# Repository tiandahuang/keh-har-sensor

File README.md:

# A Kinetic Energy Harvesting (KEH) sensor for Human Activity Recognition (HAR)
 
Design files for my thesis titled "Design of a Batteryless Sensor for Human Activity Recognition", submitted May 2024 towards an MS in Electrical and Computer Engineering at the University of Texas Austin and advised by Dr. Radu Marculescu.

## Abstract

Recent advancements in sensing technology coupled with the proliferation of
cheap, low power computing have enabled the growing popularity of wearable sensors
in everyday activities. Inertial sensing, particularly for human activity recognition
(HAR), has emerged as a ubiquitous tool across fitness, healthcare, and entertainment
applications. However, conventional wearable sensors rely on batteries, introducing
limitations in cost, environmental impact, and user burden.

This thesis explores a solution to the limitations of battery-powered operation
with the design and implementation of a wearable, kinetic energy harvesting (KEH)
powered wireless inertial sensor for batteryless HAR. The KEH-powered sensor is
energy optimized to require only 140µJ per set of accelerometer samples, translating
to an average power draw of 90µJ during continuous operation. The idle power
consumption is only 9.2µW while connected over Bluetooth. Energy harvesting is
achieved by a rotational unbalanced mass electromagnetic harvester with a peak
power output of 1.3mW.

## Device Summary

#### The full device assembly: The device is designed and assembled entirely from scratch. 

#### Component view of the entire device. Enclosures are located on the top row. There are four functional components, split between the Kinetic Energy Harvesting (KEH) Module (offset mass, rotor, stator), and the Power Conversion and Sensing/Communication Modules (PCB).

#### Full device block diagram. Energy harvested by the KEH Module (left) is converted to usable power by the Power Module (middle), which is used to sample an accelerometer and to transmit data by the Sensing Module (right). Energy storage capacitors buffer the usable power.

## Physical Design

*Files are located in `./3d/*`*

The physical operation the device centers around the KEH Module, custom-designed to address the relatively high power requirements and tight space constraints of the wearable KEH sensor. The KEH Module is a rotational unbalanced mass EM harvester; this type of harvester is implemented using a statically-mounted stator and a rotor containing a permanent magnet and an attached offset mass. 

The KEH Module and its enclosure are primarily comprised of 3D-printed polylactic acid (PLA) thermoplastic. The top of the KEH Module is a 3mm acrylic panel, stiffening the assembly and providing stability to the top of the rotor. The stator and rotor are retrieved from a 28BYJ-48 geared unipolar stepper motor. For this application, the gears are removed and the stator is modified to be bipolar. The offset mass is also constructed from PLA, with steel M3 screws and fasteners for added weight. The mass totals 8.7g with a radius of 20mm.

## Firmware Design

*Files are located in `./firmware/*`*

The firmware architecture of device adheres to an event-driven paradigm, with a target of minimizing processor occupancy. By transferring execution context between various hardware-driven interrupt handlers, the total amount of processing time can be reduced. 

Initialization must be separated into a low-level initialization and BLE initialization
due to the significant power requirements of BLE: BLE initialization includes connecting to a listening device, which has an energy budget orders of magnitude higher than low-level initialization. 

After initialization is completed (including completing a BLE connection),
context is fully transferred to a series of hardware-driven interrupts. In steady-state
operation, all system execution is triggered by a periodic timer interrupt running every
100ms. The interrupt handler initiates ADC sampling; upon completion of the ADC
sample a subsequent hardware interrupt is triggered, executing energy-monitoring
logic. If energy is sufficient for the accelerometer to sample a set of data and for a
BLE packet to be sent, the accelerometer is woken up. Running independently of the
MCU, the accelerometer stores 16 samples of data within an internal first-in-first-out
buffer (FIFO). The filling of this FIFO then triggers a hardware interrupt in the
MCU, signaling the MCU to retrieve the FIFO data and to transmit the data over
BLE.

## Electrical Design

*Files are located in `./pcb/*`*

A single PCB contains all electrical circuitry required for operation. This can be segmented into two modules, the Power Conversion Module and the Sensing/Communication Module. The Power Module contains the PMIC and energy storage; the Sensing Module contains the MCU and the accelerometer. 

### Power Conversion Module

The Power Module performs a wide array of power regulation-related functions, needed to convert the KEH generator's low and variable peak-to-peak output voltage into a stable, usable VDD for the Sensing Module. The following functions are included:

1. **Amplification**: Coupled inductors and a transformer driver (similar in topology to an isolated synchronous boost converter) amplify the weak voltage output from the generator into a high peak-to-peak AC signal; this reduces diode voltage losses from rectification.
2. **Rectification**: A full-wave rectifier converts the input AC voltage into DC. This DC voltage must be high enough to step down to the final VDD.
3. **Step-Down Conversion & Regulation**: A switching regulator steps down the unstable DC output from the rectifier to the final VDD.
4. **Charge Management**: A bidirectional gate switches between charging storage capacitors (with excess energy) and discharging storage capacitors.

### Sensing/Communication Module

The Sensing Module contains an SPI-enabled triaxial accelerometer and a BLE MCU. Electrically, the implementation follows their respective datasheets.

### Major Components

| **Component** | **Part Number** |                   **Purpose**                  |
|:-------------:|:---------------:|:----------------------------------------------:|
|      PMIC     |     LTC3109     |       Power rectification and management       |
|    BLE/MCU    |     nRF52811    |        System control, data transmission       |
| Accelerometer |      BMA400     | Triaxial acceleration sampling, data buffering |

## Power Performance

### Power Generation

| **Measurement** | **Value** |
|:---------------:|:---------:|
|   Peak Voltage  |   350 mV  |
|   Peak Current  |    4 mA   |
|    Peak Power   |   1.3 mW  |

### Power Consumption

|         **Event**        | **Value** |
|:------------------------:|:---------:|
|          Inrush          |   23 µJ   |
|  Hardware Initialization |   48 µJ   |
|    BLE Initialization    |   620 µJ  |
|        ADC Sample        |  0.88 µJ  |
| Accelerometer & BLE Send |   102 µJ  |
|   Leakage (Device Idle)  |   9.2 µW  |
|  Leakage (Open Circuit)  |    6 µW   |

## File Structure

| **Folder** | **Description**                          | **Tool/Toolchain** |
|------------|------------------------------------------|--------------------|
| ./firmware | Device firmware and project files        | SEGGER 5.42a       |
| ./pcb      | PCB schematic, layout, and project files | KiCAD 7.0          |
| ./3d       | CAD files for generator and enclosures   | SOLIDWORKS 2022    |

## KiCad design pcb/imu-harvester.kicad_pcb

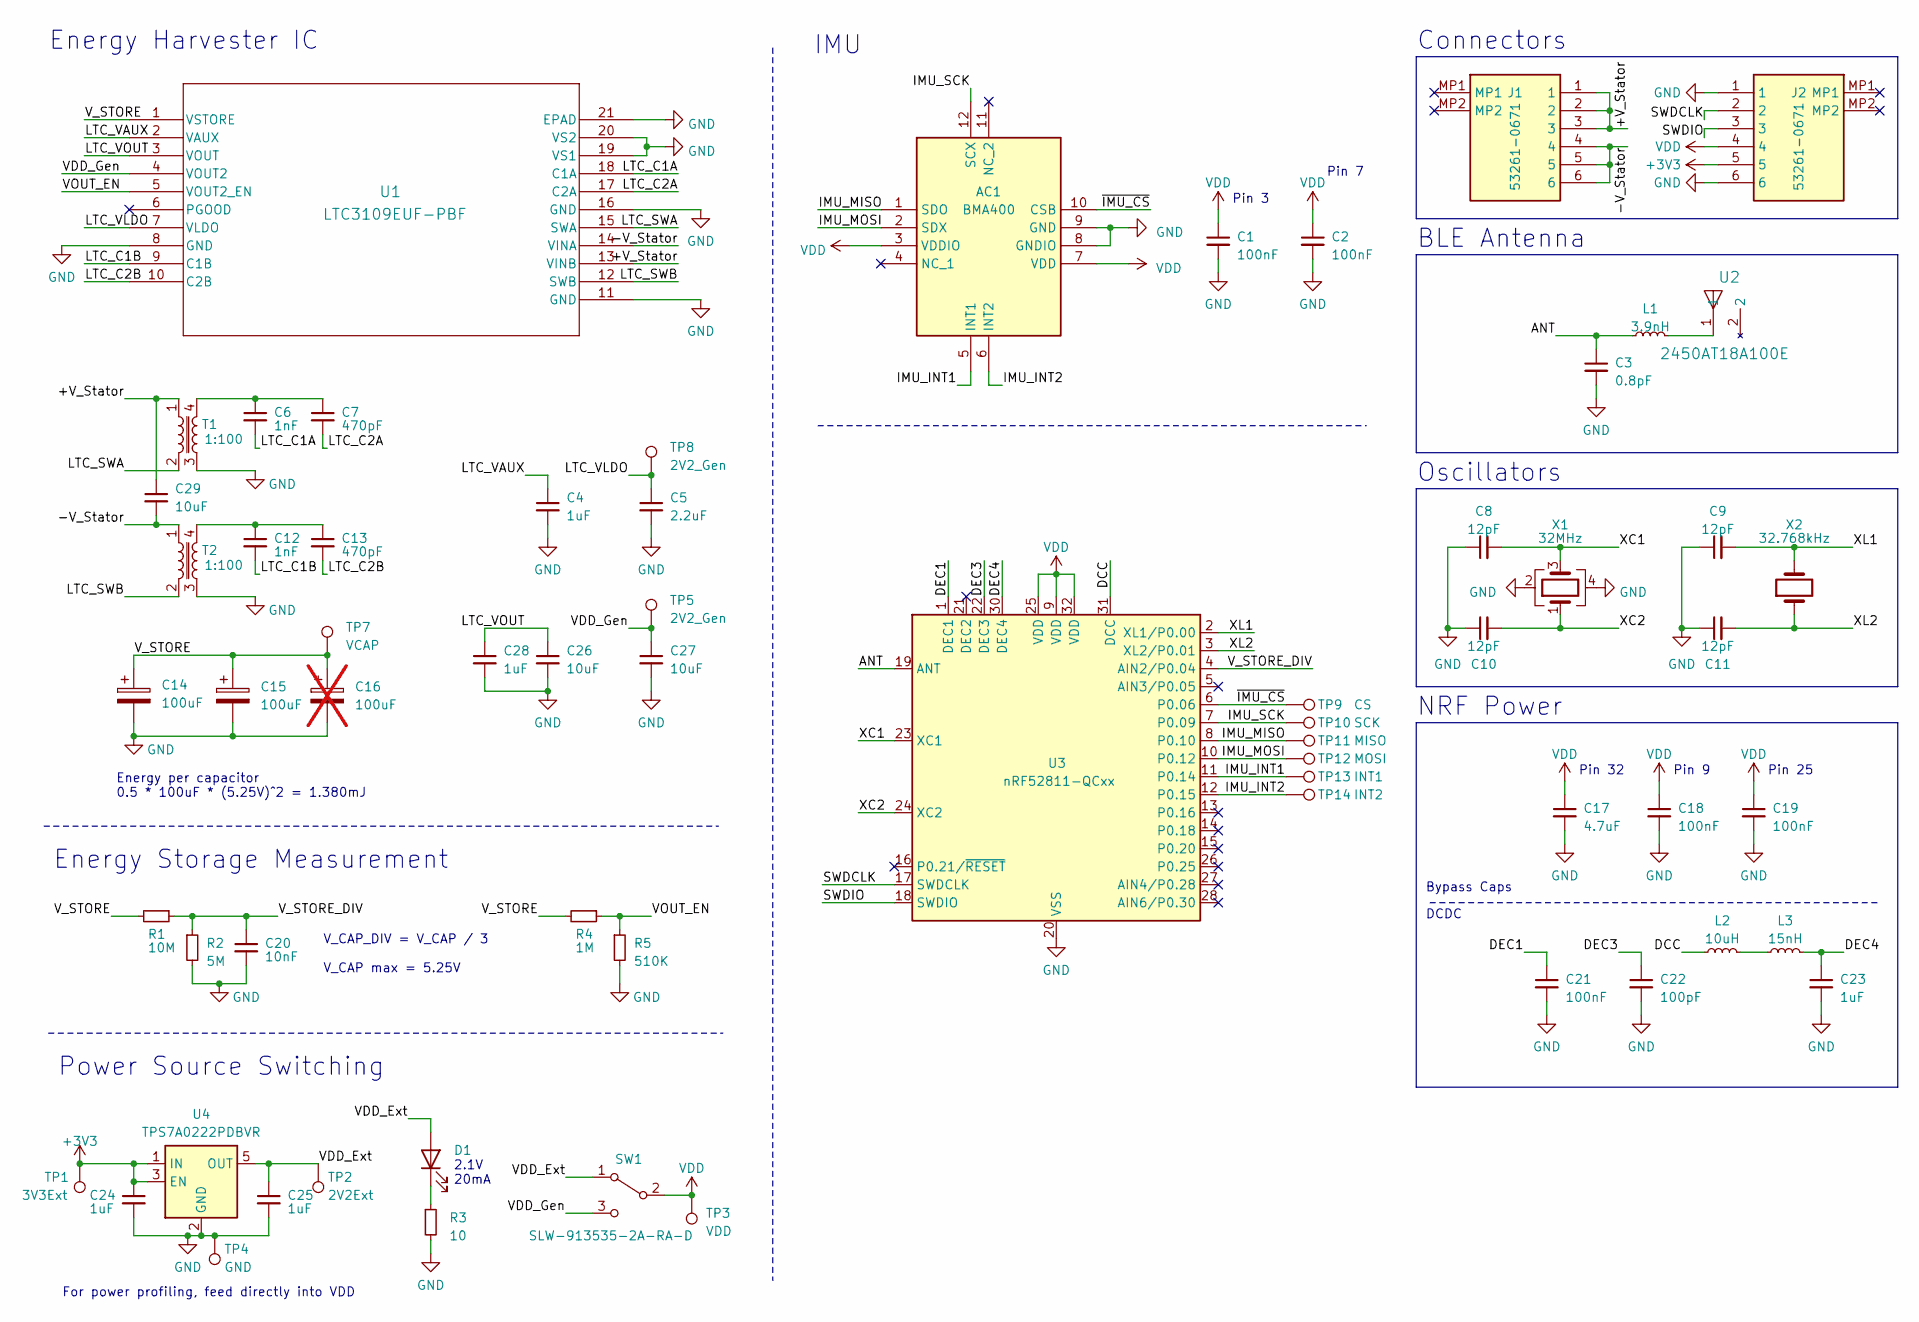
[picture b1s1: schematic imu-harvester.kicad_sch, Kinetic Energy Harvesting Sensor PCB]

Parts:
AC1: BMA400; BOSCH_LGA-12; Mouser Part Number 262-BMA400
C1, C2, C18, C19, C21: 100nF; C_0402_1005Metric; Manufacturer_Part_Number KGM05AR71C104KN
C3: 0.8pF; C_0402_1005Metric; Manufacturer_Part_Number GRM1555C1ER80BA01D
C4, C23, C24, C25, C28: 1uF; C_0402_1005Metric; Manufacturer_Part_Number CM05X7R105K06AH-HE
C5: 2.2uF; C_0402_1005Metric; Manufacturer_Part_Number GRM155Z71A225KE01D
C6, C12: 1nF; C_0402_1005Metric; Manufacturer_Part_Number C0402C102KCRACAUTO
C7, C13: 470pF; C_0402_1005Metric; Manufacturer_Part_Number KGM05ACG1H471JH
C8, C9, C10, C11: 12pF; C_0402_1005Metric; Manufacturer_Part_Number KGM05ACG1H120JN
C14: 100uF; CP_EIA-6032-28_Kemet-C; Manufacturer_Part_Number TL3C107K010C0200
C15: 100uF; CP_EIA-6032-28_Kemet-C
C16: 100uF; CP_EIA-6032-28_Kemet-C; not fitted
C17: 4.7uF; C_0603_1608Metric; Manufacturer_Part_Number GRM188Z71C475KE21D
C20: 10nF; C_0402_1005Metric; Manufacturer_Part_Number C0402C103K1RACAUTO
C22: 100pF; C_0402_1005Metric; Manufacturer_Part_Number KGM05ACG1H101JN
C26, C29: 10uF; C_0402_1005Metric; Manufacturer_Part_Number CM05X7R105K06AH-HE
C27: 10uF; C_0402_1005Metric; Manufacturer_Part_Number GRM155Z71A225KE01D
D1: LO Q976.01-P2R2-25-1; LED_0603_1608Metric; Manufacturer_Part_Number LO Q976.01-P2R2-25-1
J1, J2: 53261-0671; 532610671; Mouser Part Number 538-53261-0671
L1: 3.9nH; L_0402_1005Metric; Manufacturer_Part_Number LQG15WZ3N9B02D
L2: 10uH; L_0603_1608Metric; Manufacturer_Part_Number KLZ1608MHR100WTD25
L3: 15nH; L_0402_1005Metric; Manufacturer_Part_Number LQG15WZ15NG02D
R1: 10M; R_0402_1005Metric; Manufacturer_Part_Number RCC040210M0FKED
R2: 5M; R_0402_1005Metric; Manufacturer_Part_Number CRCW04024M99FKED
R3: 10; R_0402_1005Metric; Manufacturer_Part_Number RCC040210R0FKED
R4: 1M; R_0402_1005Metric; Manufacturer_Part_Number RCC040210M0FKED
R5: 510K; R_0402_1005Metric; Manufacturer_Part_Number CRCW04024M99FKED
SW1: SLW-913535-2A-RA-D; Manufacturer_Part_Number SLW-913535-2A-RA-D
T1, T2: 1:100; 74488540070; Manufacturer_Part_Number 74488540070
TP1: 3V3Ext; Testpoint_Hex_D3.0
TP2: 2V2Ext; Testpoint_Hex_D3.0
TP3: VDD; Testpoint_Hex_D3.0
TP4: GND; Testpoint_Hex_D3.0
TP5, TP8: 2V2_Gen; TestPoint_Pad_D1.0mm
TP7: VCAP; TestPoint_Pad_D1.0mm
TP9: CS; TestPoint_Pad_D1.0mm
TP10: SCK; TestPoint_Pad_D1.0mm
TP11: MISO; TestPoint_Pad_D1.0mm
TP12: MOSI; TestPoint_Pad_D1.0mm
TP13: INT1; TestPoint_Pad_D1.0mm
TP14: INT2; TestPoint_Pad_D1.0mm
U1: LTC3109EUF-PBF; QFN-20_UF_LIT; Manufacturer_Part_Number LTC3109EUF#PBF
U2: 2450AT18A100E; 2450AT18A100E_JOT; Manufacturer_Part_Number 2450AT18A100E
U3: nRF52811-QCxx; QFN-32-1EP_5x5mm_P0.5mm_EP3.6x3.6mm_ThermalVias; Manufacturer_Part_Number nRF52811-QCAA-R
U4: TPS7A0222PDBVR; SOT-23-5; Manufacturer_Part_Number TPS7A0222PDBVR
X1: 32MHz; Crystal_SMD_2016-4Pin_2.0x1.6mm; Manufacturer_Part_Number ECS-320-8-37B2-JTY-TR
X2: 32.768kHz; Crystal_SMD_2012-2Pin_2.0x1.2mm; Manufacturer_Part_Number ECS-.327-9-12R-TR

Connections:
+3V3: C24.1, J2.5, TP1.1, U4.1 (IN), U4.3 (EN)
/+V_Stator: C29.1, J1.1, J1.2, J1.3, T1.1, U1.13 (VINB)
/-V_Stator: C29.2, J1.4, J1.5, J1.6, T2.1, U1.14 (VINA)
/ANT: C3.1, L1.1, U3.19 (ANT)
/DCC: L2.1, U3.31 (DCC)
/DEC1: C21.1, U3.1 (DEC1)
/DEC3: C22.1, U3.22 (DEC3)
/DEC4: C23.1, L3.2, U3.30 (DEC4)
/IMU_INT1: AC1.5 (INT1), TP13.1, U3.11 (P0.14)
/IMU_INT2: AC1.6 (INT2), TP14.1, U3.12 (P0.15)
/IMU_MISO: AC1.1 (SDO), TP11.1, U3.8 (P0.10)
/IMU_MOSI: AC1.2 (SDX), TP12.1, U3.10 (P0.12)
/IMU_SCK: AC1.12 (SCX), TP10.1, U3.7 (P0.09)
/LTC_C1A: C6.2, U1.18 (C1A)
/LTC_C1B: C12.2, U1.9 (C1B)
/LTC_C2A: C7.2, U1.17 (C2A)
/LTC_C2B: C13.2, U1.10 (C2B)
/LTC_SWA: T1.2, U1.15 (SWA)
/LTC_SWB: T2.2, U1.12 (SWB)
/LTC_VAUX: C4.1, U1.2 (VAUX)
/LTC_VLDO: C5.1, TP8.1, U1.7 (VLDO)
/LTC_VOUT: C26.1, C28.1, U1.3 (VOUT)
/SWDCLK: J2.2, U3.17 (SWDCLK)
/SWDIO: J2.3, U3.18 (SWDIO)
/VDD_Ext: C25.1, D1.2 (A), SW1.1 (A), TP2.1, U4.5 (OUT)
/VDD_Gen: C27.1, SW1.3 (C), TP5.1, U1.4 (VOUT2)
/VOUT_EN: R4.1, R5.1, U1.5 (VOUT2_EN)
/V_STORE: C14.1, C15.1, C16.1, R1.2, R4.2, TP7.1, U1.1 (VSTORE)
/V_STORE_DIV: C20.1, R1.1, R2.1, U3.4 (AIN2/P0.04)
/XC1: C8.2, U3.23 (XC1), X1.3
/XC2: C10.2, U3.24 (XC2), X1.1
/XL1: C9.2, U3.2 (XL1/P0.00), X2.2
/XL2: C11.2, U3.3 (XL2/P0.01), X2.1
/~IMU_CS: AC1.10 (CSB), TP9.1, U3.6 (P0.06)
GND: AC1.8 (GNDIO), AC1.9 (GND), C1.2, C2.2, C3.2, C4.2, C5.2, C8.1, C9.1, C10.1, C11.1, C14.2, C15.2, C16.2, C17.2, C18.2, C19.2, C20.2, C21.2, C22.2, C23.2, C24.2, C25.2, C26.2, C27.2, C28.2, J2.1, J2.6, R2.2, R3.2, R5.2, T1.3, T2.3, TP4.1, U1.8 (GND), U1.11 (GND), U1.16 (GND), U1.19 (VS1), U1.20 (VS2), U1.21 (EPAD), U3.20 (VSS), U3.29 (VSS), U3.33 (VSS), U4.2 (GND), X1.2, X1.4
unnamed: C6.1, C7.1, T1.4
unnamed: C12.1, C13.1, T2.4
unnamed: D1.1 (K), R3.1
unnamed: L1.2, U2.1
unnamed: L2.2, L3.1
VDD: AC1.3 (VDDIO), AC1.7 (VDD), C1.1, C2.1, C17.1, C18.1, C19.1, J2.4, SW1.2 (B), TP3.1, U3.9 (VDD), U3.25 (VDD), U3.32 (VDD)

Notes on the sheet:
V_CAP_DIV = V_CAP / 3 V_CAP max = 5.25V
Energy Storage Measurement
Pin 3
Power Source Switching
Pin 9
NRF Power
Connectors
DCDC
IMU
2.1V 20mA
Bypass Caps
BLE Antenna
Oscillators
Energy per capacitor 0.5 * 100uF * (5.25V)^2 = 1.380mJ
Pin 32
For power profiling, feed directly into VDD
Pin 25
Energy Harvester IC
Pin 7

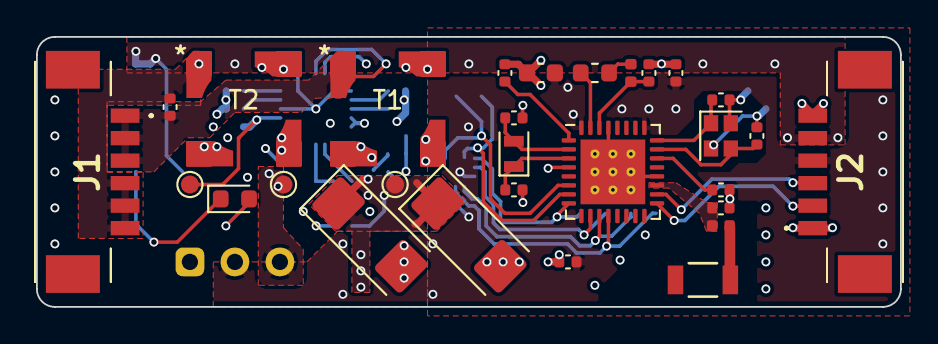
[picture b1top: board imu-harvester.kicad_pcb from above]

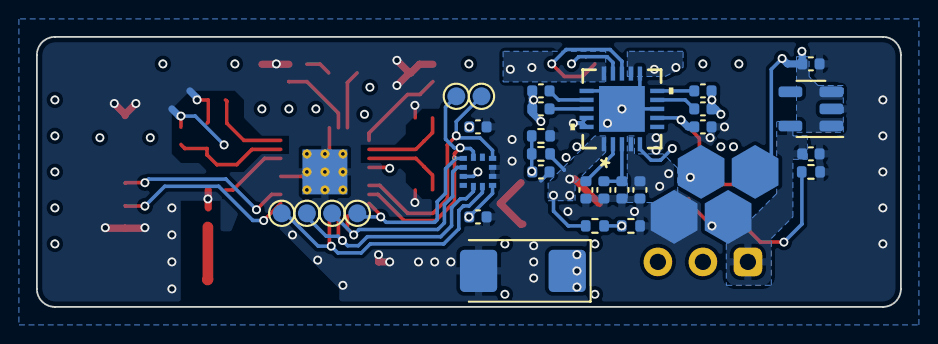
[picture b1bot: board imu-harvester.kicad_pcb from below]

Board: 4 copper layers, 48.0 x 15.0 mm, 63 parts (33 on the bottom side), 41 nets.

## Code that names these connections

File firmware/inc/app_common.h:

/**
 * common includes and configurations
*/

#pragma once

#include <string.h>
#include <stdlib.h>
#include <stdint.h>
#include <stdbool.h>
#include <inttypes.h>
#include "nordic_common.h"
#include "app_util.h"
#include "app_timer.h"


// config
#define V_STORE_DIV_INV         3           // v_store_div = v_store / V_STORE_DIV_INV
#define V_STORE_SAMP_PERIOD_MS  100

// voltage thresholds. resolution is ~21mV
#define V_STORE_LVL_BLE_INIT    2200        // run BLE init once storage cap is at 2.2V = 242uJ
#define V_STORE_LVL_SAMPLE      1800        // sample + send once storage cap is at 1.8V = 162uJ

// GPIO config
#define GPIO_V_STORE_DIV_IN     NRF_SAADC_INPUT_AIN2    // capacitor voltage -- this is on P.04/AIN2 (which expands to 3...)
#define GPIO_DIV_EN             5           // enable capacitor voltage divider

#define SPI_SCK                 9
#define SPI_MISO                10
#define SPI_MOSI                12

#define IMU_CS                  6
#define IMU_INT1                14
#define IMU_INT2                15

// test config
#define POWER_PROFILING_ENABLED 0           // enable power profiling -- runs IMU sample and BLE send on loop
#define POWER_PROFILING_PERIOD_MS 500       // period of power profiling loop

// BLE config
#define DEVICE_NAME_DEFAULT     "test"      // device name in BLE advertising
#define ENABLE_DEVICE_NAME      1           // enable device name in advertising

#define APP_ADV_INTERVAL        MSEC_TO_UNITS(20, UNIT_0_625_MS)    // advertising interval (in units of 0.625 ms)
#define APP_ADV_DURATION        MSEC_TO_UNITS(200, UNIT_10_MS)      // advertising duration (in units of 10 milliseconds)
#define MIN_CONN_INTERVAL       MSEC_TO_UNITS(8,  UNIT_1_25_MS)     /**< Minimum acceptable connection interval (20 ms), Connection interval uses 1.25 ms units. */
#define MAX_CONN_INTERVAL       MSEC_TO_UNITS(12, UNIT_1_25_MS)     /**< Maximum acceptable connection interval (75 ms), Connection interval uses 1.25 ms units. */
#define SLAVE_LATENCY           150                                 /**< Slave latency. */
#define CONN_SUP_TIMEOUT        MSEC_TO_UNITS(30000, UNIT_10_MS)    /**< Connection supervisory timeout (4 seconds), Supervision Timeout uses 10 ms units. */
#define FIRST_CONN_PARAMS_UPDATE_DELAY APP_TIMER_TICKS(50) /**< Time from initiating event (connect or start of notification) to first time sd_ble_gap_conn_param_update is called (5 seconds). */
#define NEXT_CONN_PARAMS_UPDATE_DELAY APP_TIMER_TICKS(30000) /**< Time between each call to sd_ble_gap_conn_param_update after the first call (30 seconds). */
#define MAX_CONN_PARAMS_UPDATE_COUNT 1                       /**< Number of attempts before giving up the connection parameter negotiation. */

#define QWR_BUFFER_SIZE                 512

#define SEC_PARAM_BOND                  1                                       //!< Perform bonding.
#define SEC_PARAM_MITM                  0                                       //!< Man In The Middle protection not required.
#define SEC_PARAM_LESC                  0                                       //!< LE Secure Connections not enabled.
#define SEC_PARAM_KEYPRESS              0                                       //!< Keypress notifications not enabled.
#define SEC_PARAM_IO_CAPABILITIES       BLE_GAP_IO_CAPS_NONE                    //!< No I/O capabilities.
#define SEC_PARAM_OOB                   0                                       //!< Out Of Band data not available.
#define SEC_PARAM_MIN_KEY_SIZE          7                                       //!< Minimum encryption key size.
#define SEC_PARAM_MAX_KEY_SIZE          16                                      //!< Maximum encryption key size.

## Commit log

2024-05-14 readme
2024-05-14 Add project files
2024-05-15 preview
